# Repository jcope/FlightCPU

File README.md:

# FlightCPU
An embedded data logger for high altitude balloons

The Flight CPU is designed as a data logger for High Altitude Balloons. It is designed around the ATMEGA328P so it can easily be developed using Arduino tools. Most sensor modules communicate with the uC using I2C with the exception of the Humidity/Temp sensor which uses SPI. The data is then logged on the MicroSD card. 

Sensors include: Gyroscope, Compass, Temp/Humidity, Barometer.

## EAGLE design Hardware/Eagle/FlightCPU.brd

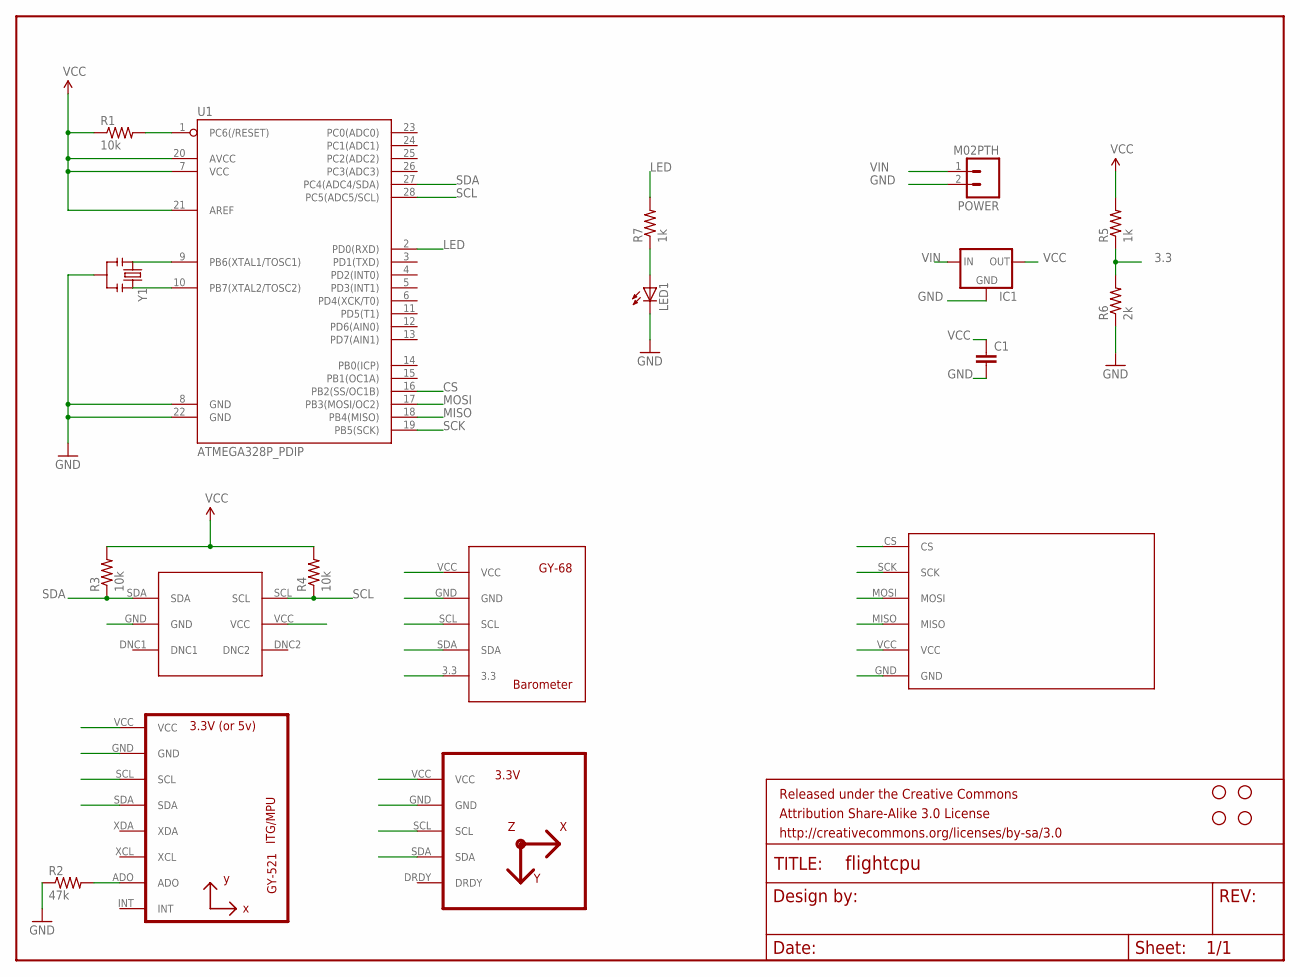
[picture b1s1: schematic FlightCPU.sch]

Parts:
C1: CAPKIT; CAP-PTH-SMALL-KIT
FRAME1: FRAME-LETTER; CREATIVE_COMMONS
IC1: V_REG_78XXSIDE; 78XXL
LED1: LED3MM
POWER: M02PTH; 1X02
R1, R3, R4: 10k; AXIAL-0.3
R2: 47k; AXIAL-0.3
R5, R7: 1k; AXIAL-0.3
R6: 2k; AXIAL-0.3
STANDOFF1, STANDOFF2, STANDOFF3, STANDOFF4: STAND-OFF
U1: ATMEGA328P_PDIP; DIL28-3
U2: GY-521MPU6050; GY-521
U3: HMC5883LGY-271; GY-271
U$1: SI7020_DIP; SI7020
U$2: GY-68
U$3: MICRO_SD; MICROSD
Y1: RESONATORPTH; RESONATOR-PTH

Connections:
3.3: R5.P$1 (1), R6.P$2 (2), U$2.3.3
CS: U1.16 (PB2(SS/OC1B)), U$3.CS
GND: C1.2, IC1.GND, LED1.K (C), POWER.2, R2.P$1 (1), R6.P$1 (1), U1.8 (GND), U1.22 (GND), U2.GND, U3.GND, U$1.GND, U$2.GND, U$3.GND, Y1.2
LED: R7.P$2 (2), U1.2 (PD0(RXD))
MISO: U1.18 (PB4(MISO)), U$3.MISO
MOSI: U1.17 (PB3(MOSI/OC2)), U$3.MOSI
unnamed: R1.P$2 (2), U1.1 (PC6(/RESET))
unnamed: U1.9 (PB6(XTAL1/TOSC1)), Y1.1
unnamed: U1.10 (PB7(XTAL2/TOSC2)), Y1.3
unnamed: LED1.A, R7.P$1 (1)
unnamed: R2.P$2 (2), U2.ADO
SCK: U1.19 (PB5(SCK)), U$3.SCK
SCL: R4.P$1 (1), U1.28 (PC5(ADC5/SCL)), U2.SCL, U3.SCL, U$1.SCL, U$2.SCL
SDA: R3.P$1 (1), U1.27 (PC4(ADC4/SDA)), U2.SDA, U3.SDA, U$1.SDA, U$2.SDA
VCC: C1.1, IC1.OUT, R1.P$1 (1), R3.P$2 (2), R4.P$2 (2), R5.P$2 (2), U1.7 (VCC), U1.20 (AVCC), U1.21 (AREF), U2.VCC, U3.VCC, U$1.VCC, U$2.VCC, U$3.VCC
VIN: IC1.IN, POWER.1

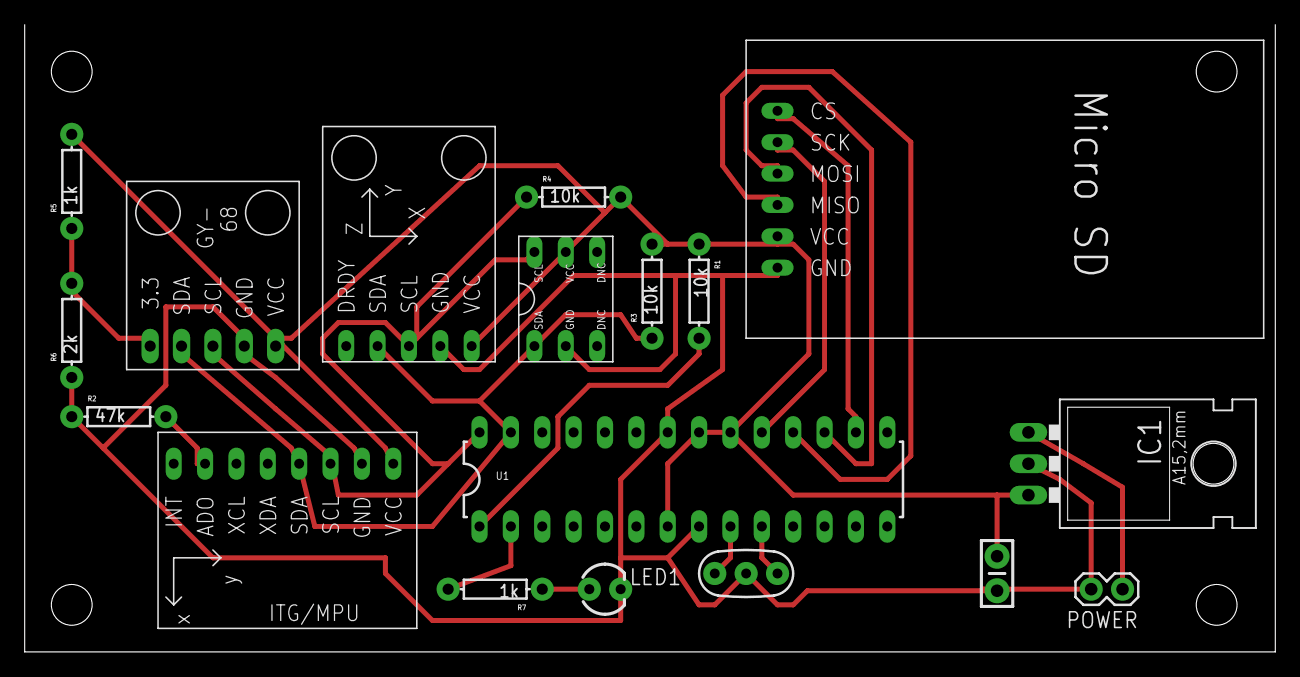
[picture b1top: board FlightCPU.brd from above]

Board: 2 copper layers, 101.3 x 50.8 mm, 23 parts (0 on the bottom side), 16 nets.

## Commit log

2016-06-07 Initial Software Commit
    Added Arduino Project File- as well as 3rd party libraries.
    Added Datasheets
2016-06-07 Initial Hardware Commit
    Added Eagle Library containing all the components, and the eagle
    project files containing the schematic and the pcb layout.
    Also added pdf containing the image used to etch the pcb.
2016-06-07 Updated ReadMe Files

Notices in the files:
parts and their libraries:
SparkFun-DigitalIC: Licensing: CC v3.0 Share-Alike You are welcome to use this library for commercial purposes.
SparkFun-Aesthetics: Released under the Creative Commons Attribution Share-Alike 3.0 License
SparkFun-Aesthetics: http://creativecommons.org/licenses/by-sa/3.0
